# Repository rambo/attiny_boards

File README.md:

View this project on [CADLAB.io](https://cadlab.io/node/904). 

# ATTiny breakout boards

Collection of various more or less prototype board designs for breaking
out SMD ATTinys.

The SMD parts are cheaper than DIP and I've grown tired of drilling holes
anyway, besides this way I can add some essential supporting hardware like
bypass caps and the ISP header on the same board (optionally also xtal)

Arduino support for these chips is available from the [arduino-tiny](https://github.com/rambo/arduino-tiny) project, 
see also [this tutorial](http://hlt.media.mit.edu/?p=1695) by High-Low Tech.

I personally have found using the ArduinoISP a bit hit-and-miss, so I suggest investing on a proper ISP (some of the clones work better
than others but I decided to get a genuine AVRISPmkII after spending an evening battling with ArduinoISP)

## The designs

  - attiny85_bo_1l.brd: this is a very quick design for ATTiny25/45/85 chips meant to be etched at home, thus in one layer. [Picture](https://picasaweb.google.com/lh/photo/0eMphjL9Uqn8iMIKu49FZNMTjNZETYmyPJy0liipFm0?feat=directlink).
  - attiny85_bo.brd: A two-layer design for ATTiny25/45/85 chips that should be generally quite usable. [Picture](https://picasaweb.google.com/lh/photo/wWMrBrGMo7IKX4xKiI6fBtMTjNZETYmyPJy0liipFm0?feat=directlink).
    - First revisions of the board had a silkscreen error, PB1 and PB2 were reversed (my bad).
    - For some reason the very first revision has much nicer silkscreen than the next, they were (likely) manufactured in different batches but I should doublecheck line widths etc.
  - attiny4313_bo.brd: A two-layer design (with a lot of vias so not really doable at home).
    - Got the boards, silkscreen is fine on these, [picture](https://picasaweb.google.com/lh/photo/29UdsFFLtWyybYlaUJ8i69MTjNZETYmyPJy0liipFm0?feat=directlink).
  - attiny84_bo.brd: A two-layer design that should be generally quite usable.
    - Got the boards, silkscreen is fine on these, [picture](https://picasaweb.google.com/lh/photo/29UdsFFLtWyybYlaUJ8i69MTjNZETYmyPJy0liipFm0?feat=directlink).
  - attiny1634_bo.brd: First revision of this board/schematic had a bug in the part definition. Thus a [trace must be cut](https://picasaweb.google.com/lh/photo/p4AA6TQTbEzGxg4LxbUNLtMTjNZETYmyPJy0liipFm0?feat=directlink) and a jumper wire added.
    - arduino-tiny support for this chip is still [experimental](https://github.com/rambo/arduino-tiny/tree/attiny1634)
  - attiny85_pogo_pgm.brd: an attempt to make a pogo-pin programming header that connects directly to ATTiny85 (SOIC) feet.
    - This proved to be rather misguided, it will require very carefull alignment rig but if I get the need of mass programming unsoldered chips I might still do it.

## TODO

  - Add diodes to protect against reverse and over -voltage (with indicator led ?)
  - simple board to break the ISP header into normal 2.54mm pitch pogo-pins in the same order (those pins unfortunately do not fit)
    into the cable connector directly), did this on stripboard and then realized dotboard would have been much better.

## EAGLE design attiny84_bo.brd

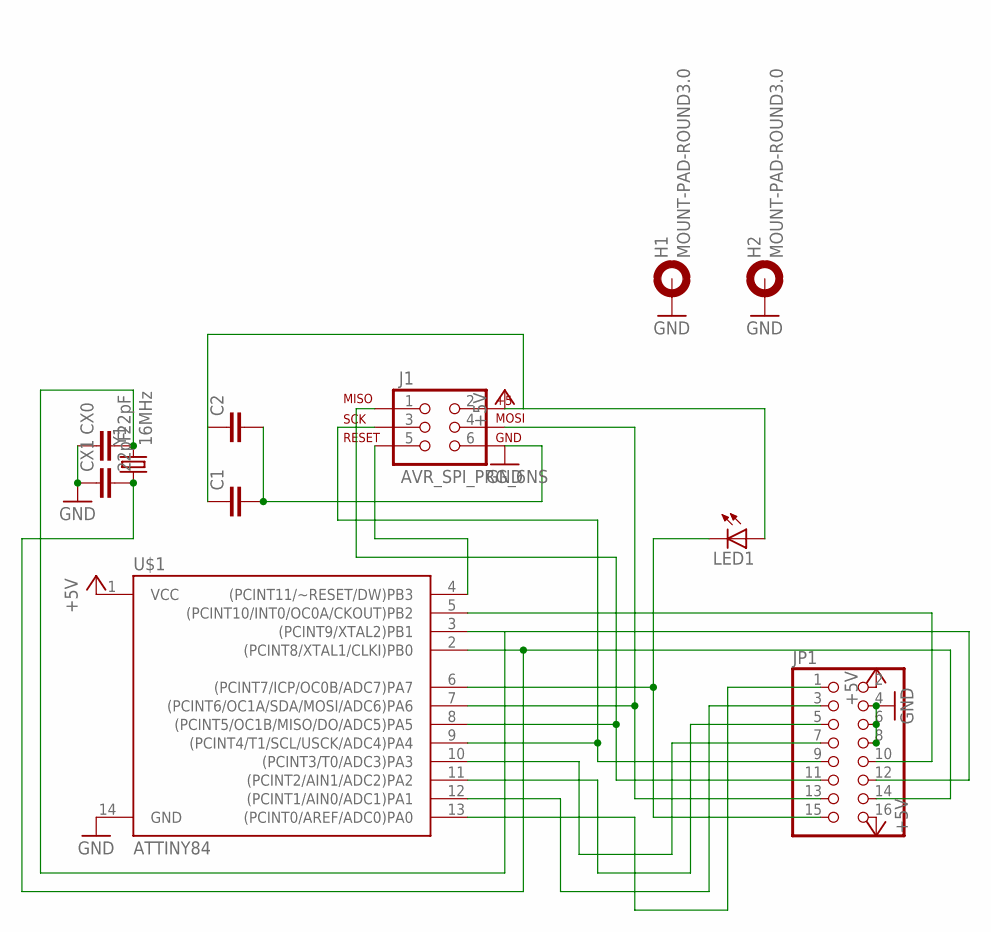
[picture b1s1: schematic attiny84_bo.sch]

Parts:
C1, C2: C-EUC0805; C0805
CX0, CX1: 22pF; C0603
H1, H2: MOUNT-PAD-ROUND3.0; 3,0-PAD
J1: AVR_SPI_PRG_6NS; 2X3-NS
JP1: PINHD-2X8; 2X08
LED1: LED0603; LED-0603
U$1: ATTINY84; SO14
Y1: 16MHz; CRYSTAL-SMD-5X3

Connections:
+5V: C1.1, C2.1, J1.2, JP1.2, JP1.16, LED1.A, U$1.1 (VCC)
GND: C1.2, C2.2, CX0.1, CX1.1, H1.B3,0, H2.B3,0, J1.6, JP1.4, JP1.6, JP1.8, U$1.14 (GND)
PA0: JP1.1, U$1.13 ((PCINT0/AREF/ADC0)PA0)
PA1: JP1.3, U$1.12 ((PCINT1/AIN0/ADC1)PA1)
PA2: JP1.5, U$1.11 ((PCINT2/AIN1/ADC2)PA2)
PA3: JP1.7, U$1.10 ((PCINT3/T0/ADC3)PA3)
PA4/SCL: J1.3, JP1.9, U$1.9 ((PCINT4/T1/SCL/USCK/ADC4)PA4)
PA5/MISO: J1.1, JP1.11, U$1.8 ((PCINT5/OC1B/MISO/DO/ADC5)PA5)
PA6/MOSI: J1.4, JP1.13, U$1.7 ((PCINT6/OC1A/SDA/MOSI/ADC6)PA6)
PA7: JP1.15, LED1.C, U$1.6 ((PCINT7/ICP/OC0B/ADC7)PA7)
PB0/XTAL1: CX1.2, JP1.14, U$1.2 ((PCINT8/XTAL1/CLKI)PB0), Y1.1
PB1/XTAL2: CX0.2, JP1.12, U$1.3 ((PCINT9/XTAL2)PB1), Y1.3 (2)
PB2: JP1.10, U$1.5 ((PCINT10/INT0/OC0A/CKOUT)PB2)
PB3/RESET-: J1.5, U$1.4 ((PCINT11/~RESET/DW)PB3)

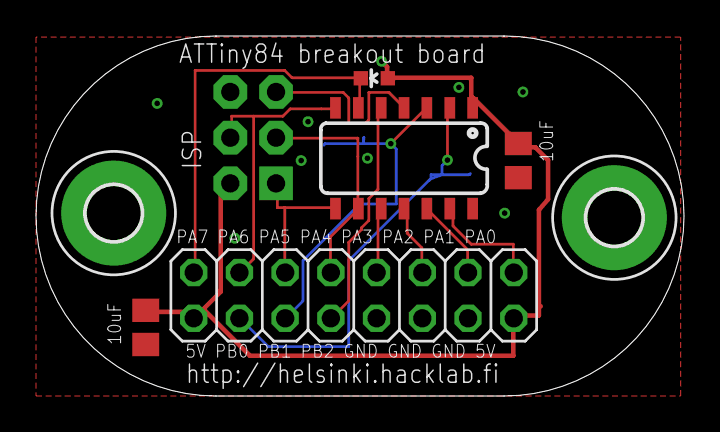
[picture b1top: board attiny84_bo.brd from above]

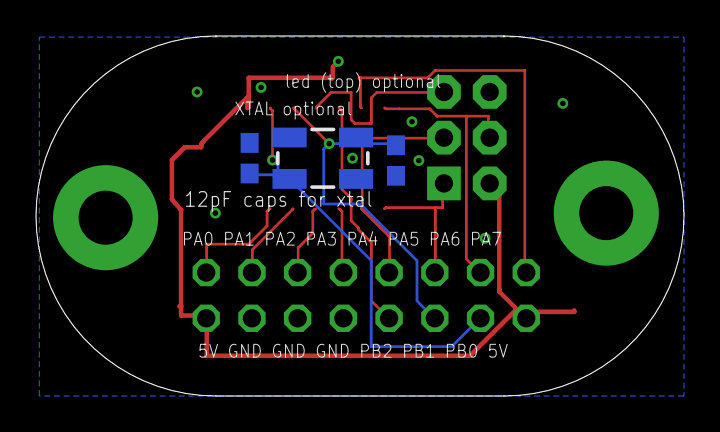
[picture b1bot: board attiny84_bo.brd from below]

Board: 2 copper layers, 36.0 x 20.0 mm, 11 parts (3 on the bottom side), 14 nets.

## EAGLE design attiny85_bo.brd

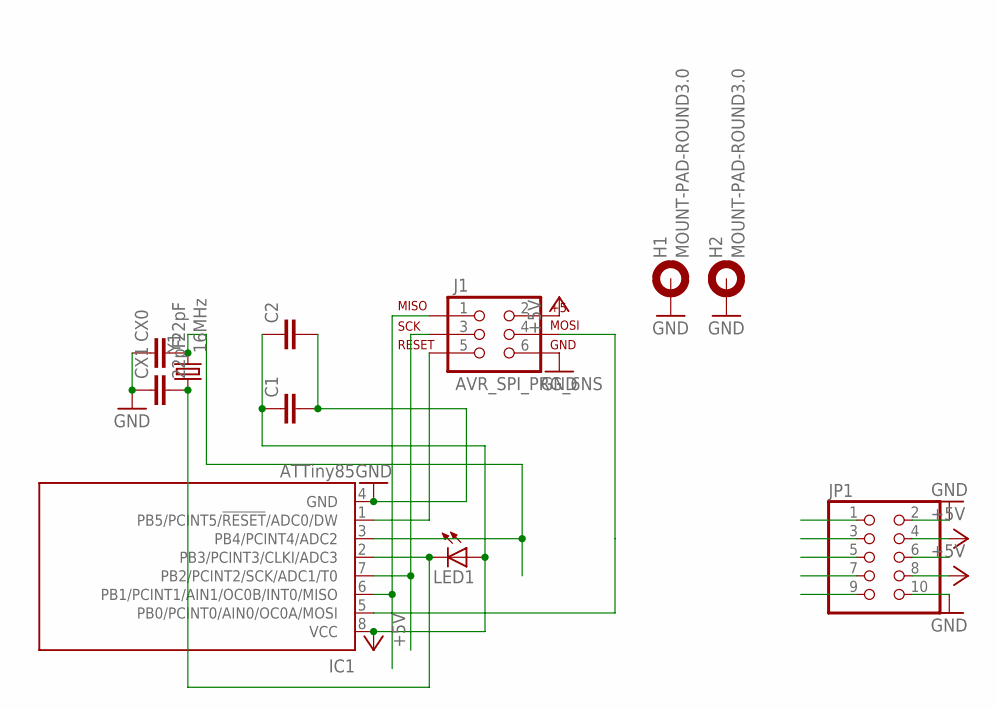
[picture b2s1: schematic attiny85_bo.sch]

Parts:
C1, C2: C-EUC0805; C0805
CX0, CX1: 22pF; C0603
H1, H2: MOUNT-PAD-ROUND3.0; 3,0-PAD
IC1: ATTiny85; 8S2
J1: AVR_SPI_PRG_6NS; 2X3-NS
JP1: PINHD-2X5; 2X05
LED1: LED0603; LED-0603
Y1: 16MHz; CRYSTAL-SMD-5X3

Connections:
+5V: C1.1, C2.1, IC1.8 (VCC), J1.2, JP1.4, JP1.8, LED1.A
GND: C1.2, C2.2, CX0.1, CX1.1, H1.B3,0, H2.B3,0, IC1.4 (GND), J1.6, JP1.2, JP1.10
PB0: IC1.5 (PB0/PCINT0/AIN0/OC0A/MOSI), J1.4, JP1.1
PB1: IC1.6 (PB1/PCINT1/AIN1/OC0B/INT0/MISO), J1.1, JP1.3
PB2: IC1.7 (PB2/PCINT2/SCK/ADC1/T0), J1.3, JP1.5
PB3: CX1.2, IC1.2 (PB3/PCINT3/CLKI/ADC3), JP1.7, LED1.C, Y1.1
PB4: CX0.2, IC1.3 (PB4/PCINT4/ADC2), JP1.9, Y1.3 (2)
PB5: IC1.1 (PB5/PCINT5/!RESET!/ADC0/DW), J1.5, JP1.6

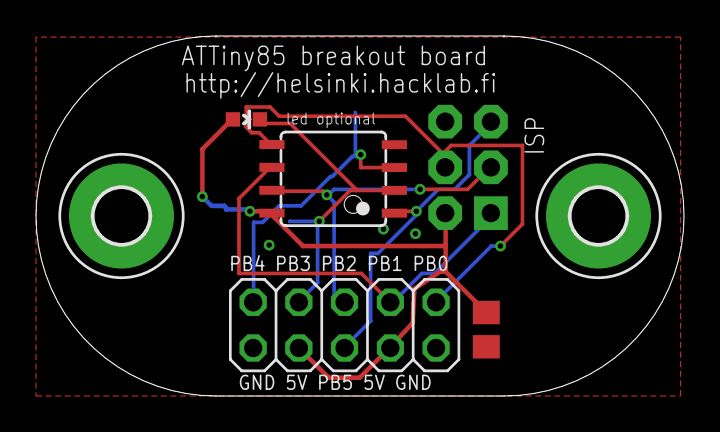
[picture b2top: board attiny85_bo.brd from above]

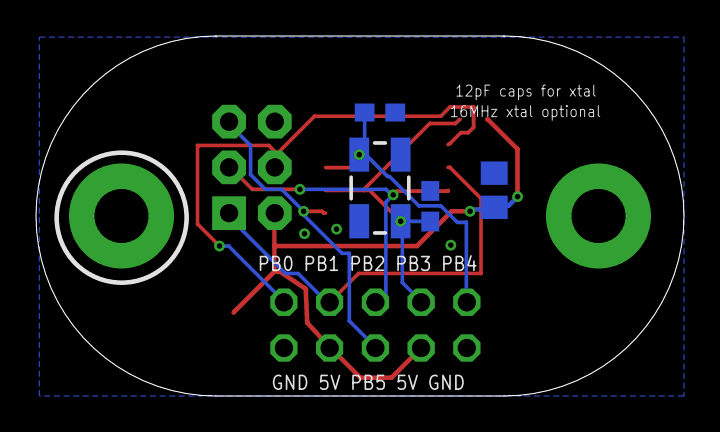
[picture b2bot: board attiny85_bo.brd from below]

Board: 2 copper layers, 36.0 x 20.0 mm, 11 parts (4 on the bottom side), 8 nets.

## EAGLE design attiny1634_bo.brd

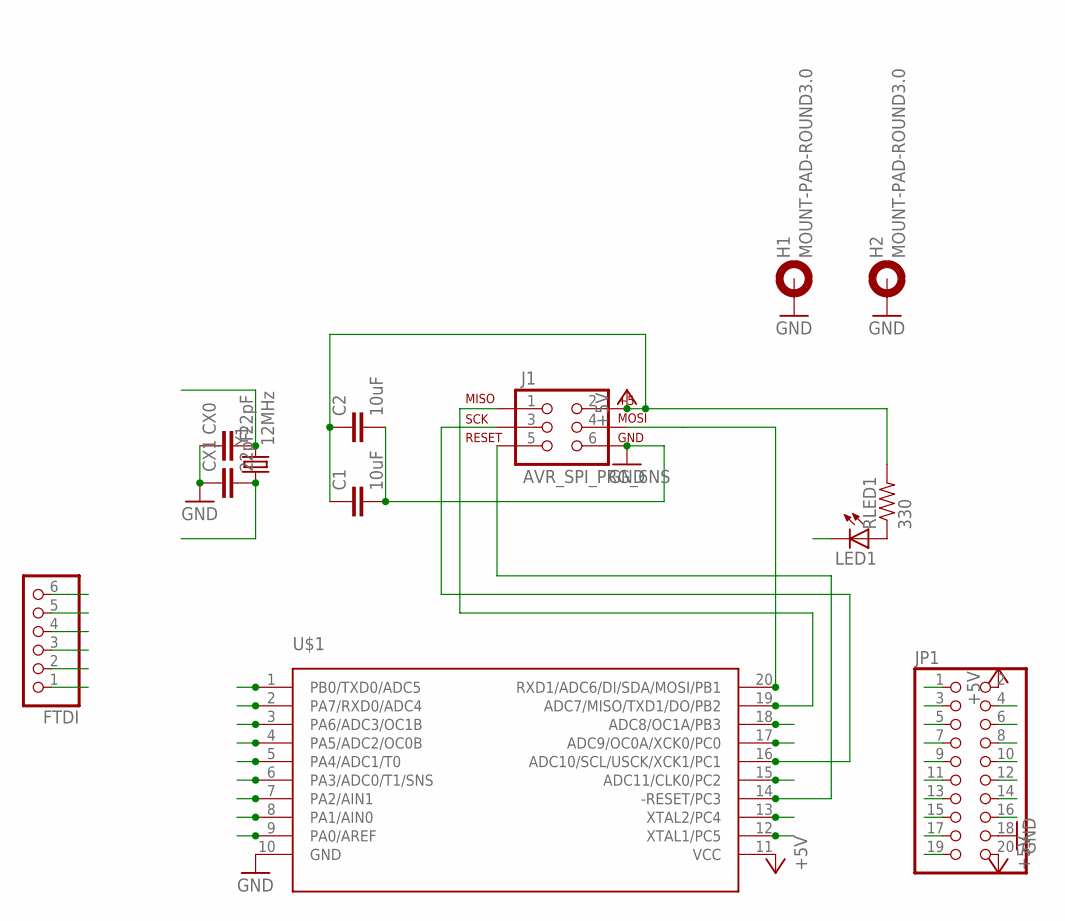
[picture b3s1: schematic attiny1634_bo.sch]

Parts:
C1, C2: 10uF; C0805
CX0, CX1: 22pF; C0603
FTDI: PINHD-1X6; 1X06
H1, H2: MOUNT-PAD-ROUND3.0; 3,0-PAD
J1: AVR_SPI_PRG_6NS; 2X3-NS
JP1: PINHD-2X10; 2X10
LED1: LED0603; LED-0603
RLED1: 330; 0603-RES
U$1: ATTINY1634; SOIC20
Y1: 12MHz; CRYSTAL-SMD-5X3

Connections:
+5V: C1.1, C2.1, FTDI.3, J1.2, JP1.2, JP1.20, RLED1.2, U$1.11 (VCC)
CTS: FTDI.2
GND: C1.2, C2.2, CX0.1, CX1.1, FTDI.1, H1.B3,0, H2.B3,0, J1.6, JP1.18, U$1.10 (GND)
unnamed: LED1.A, RLED1.1
PA0: JP1.5, U$1.9 (PA0/AREF)
PA1: JP1.7, U$1.8 (PA1/AIN0)
PA2: JP1.9, U$1.7 (PA2/AIN1)
PA3: JP1.11, U$1.6 (PA3/ADC0/T1/SNS)
PA4: JP1.13, U$1.5 (PA4/ADC1/T0)
PA5: JP1.15, U$1.4 (PA5/ADC2/OC0B)
PA6: JP1.17, U$1.3 (PA6/ADC3/OC1B)
PA7/RX0: FTDI.4, JP1.19, U$1.2 (PA7/RXD0/ADC4)
PB0/TXD0: FTDI.5, JP1.16, U$1.1 (PB0/TXD0/ADC5)
PB1/MOSI/ADC6: J1.4, JP1.14, U$1.20 (RXD1/ADC6/DI/SDA/MOSI/PB1)
PB2/ADC7/TX1: J1.1, JP1.12, U$1.19 (ADC7/MISO/TXD1/DO/PB2)
PB3/ADC8/OC1A: JP1.10, U$1.18 (ADC8/OC1A/PB3)
PC0/ADC9/OC0A: JP1.8, LED1.C, U$1.17 (ADC9/OC0A/XCK0/PC0)
PC1/SCL/ADC10: J1.3, JP1.1, U$1.16 (ADC10/SCL/USCK/XCK1/PC1)
PC2/ADC11: JP1.3, U$1.15 (ADC11/CLK0/PC2)
PC3/-RESET: FTDI.6, J1.5, U$1.14 (-RESET/PC3)
PC4/XTAL2: CX0.2, JP1.6, U$1.13 (XTAL2/PC4), Y1.3 (2)
PC5/XTAL1: CX1.2, JP1.4, U$1.12 (XTAL1/PC5), Y1.1

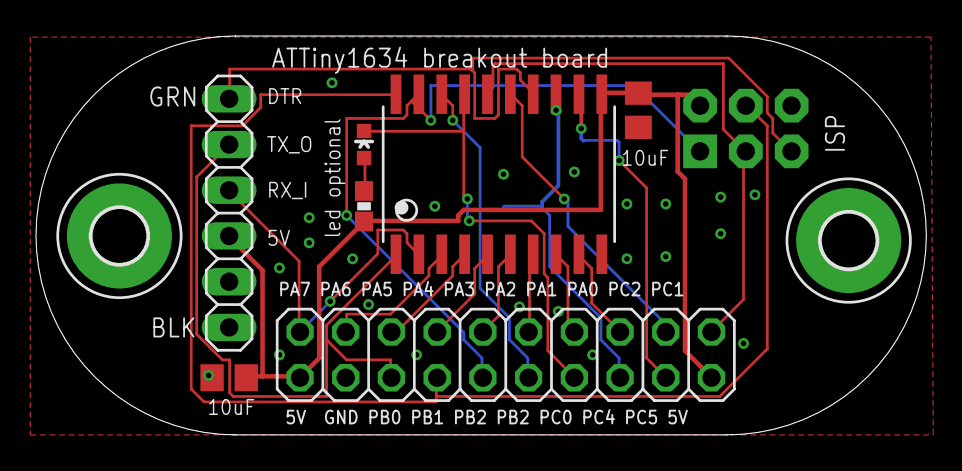
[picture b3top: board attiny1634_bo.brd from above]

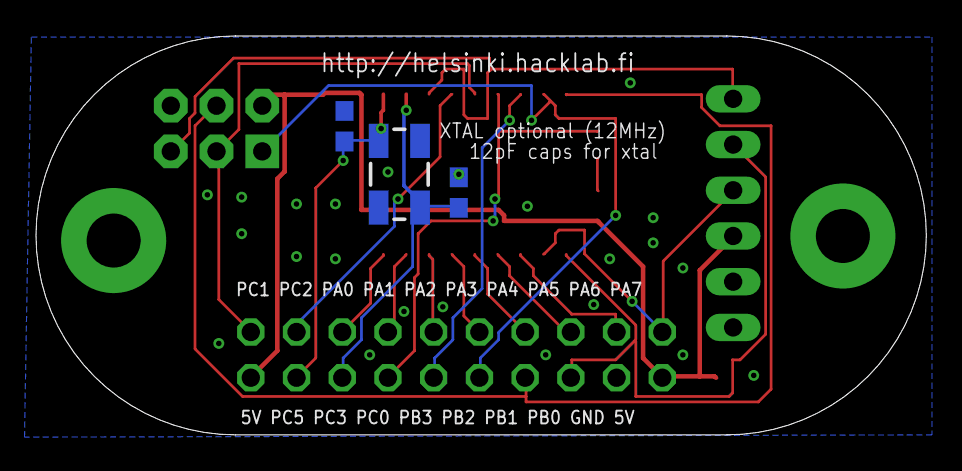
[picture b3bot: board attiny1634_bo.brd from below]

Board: 2 copper layers, 49.5 x 22.2 mm, 13 parts (3 on the bottom side), 21 nets.

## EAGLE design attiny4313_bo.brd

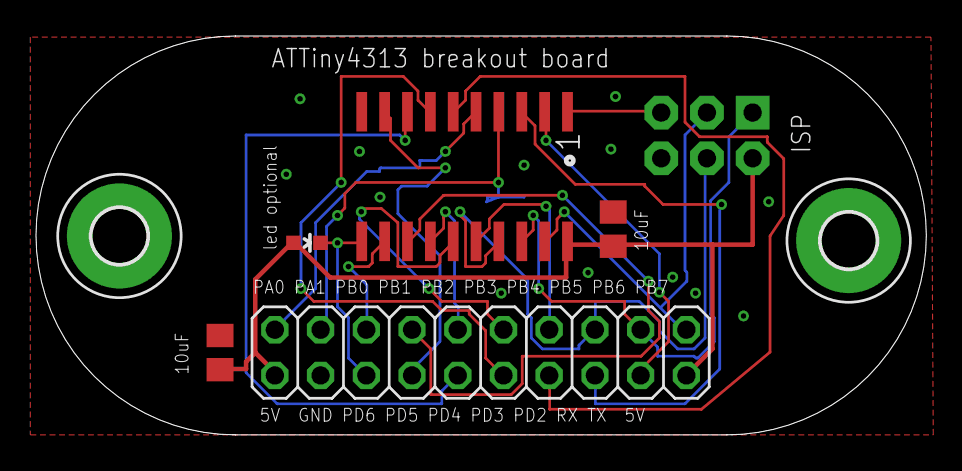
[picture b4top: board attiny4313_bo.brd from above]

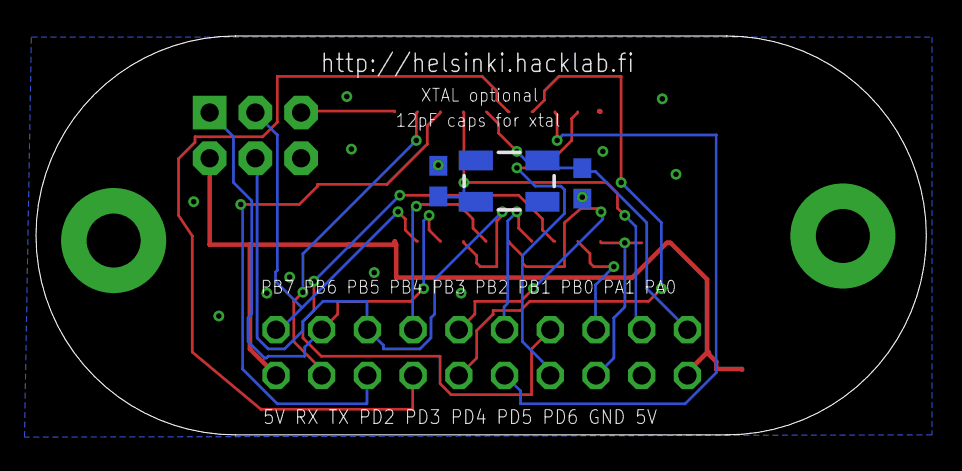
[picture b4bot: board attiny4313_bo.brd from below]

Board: 2 copper layers, 49.5 x 22.2 mm, 11 parts (3 on the bottom side), 20 nets.

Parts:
C1, C2: C0805
CX0, CX1: 22pF; C0603
H1, H2: MOUNT-PAD-ROUND3.0; 3,0-PAD
J1: AVR_SPI_PRG_6NS; 2X3-NS
JP1: 2X10
LED1: LED-0603
U$1: ATTINY2313A; SOP20
Y1: 16MHz; CRYSTAL-SMD-5X3

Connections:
+5V: C1.1, C2.1, J1.2, JP1.2, JP1.20, LED1.A, U$1.20
GND: C1.2, C2.2, CX0.1, CX1.1, H1.B3,0, H2.B3,0, J1.6, JP1.18, U$1.10
PA0/XTAL1: CX0.2, JP1.19, U$1.5, Y1.3
PA1/XTAL2: CX1.2, JP1.17, U$1.4, Y1.1
PA2/RESET-: J1.5, U$1.1
PB0: JP1.15, U$1.12
PB1: JP1.13, U$1.13
PB2: JP1.11, U$1.14
PB3: JP1.9, U$1.15
PB4: JP1.7, U$1.16
PB5/MOSI: J1.4, JP1.5, U$1.17
PB6/MISO: J1.1, JP1.3, U$1.18
PB7/SCL: J1.3, JP1.1, U$1.19
PD0/RDX: JP1.4, U$1.2
PD1/TXD: JP1.6, U$1.3
PD2: JP1.8, U$1.6
PD3: JP1.10, U$1.7
PD4: JP1.12, U$1.8
PD5: JP1.14, U$1.9
PD6: JP1.16, LED1.C, U$1.11

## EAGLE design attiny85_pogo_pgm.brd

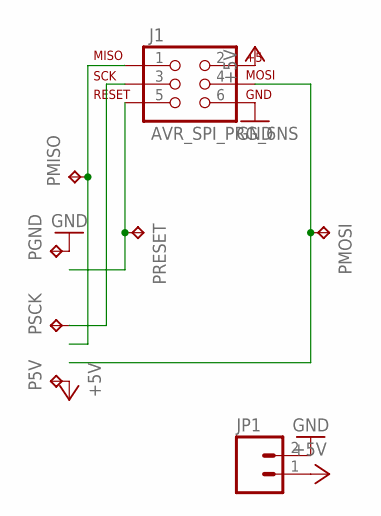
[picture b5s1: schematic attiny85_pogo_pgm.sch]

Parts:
J1: AVR_SPI_PRG_6NS; 2X3-NS
JP1: M02PTH; 1X02
P5V: TPTP12R; TP12R
PGND: TPTP12R; TP12R
PMISO: TPTP12R; TP12R
PMOSI: TPTP12R; TP12R
PRESET: TPTP12R; TP12R
PSCK: TPTP12R; TP12R

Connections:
+5V: J1.2, JP1.1, P5V.TP
GND: J1.6, JP1.2, PGND.TP
IN1/MISO: J1.1, PMISO.TP
RESET-: J1.5, PRESET.TP
SCL/SCK: J1.3, PSCK.TP
SDA/MOSI: J1.4, PMOSI.TP

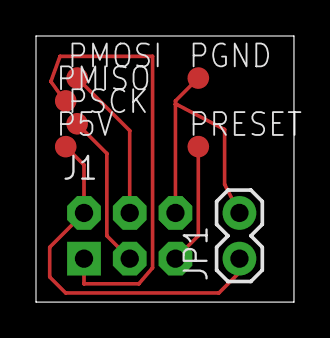
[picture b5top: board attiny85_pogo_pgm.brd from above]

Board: 1 copper layer, 14.3 x 14.8 mm, 8 parts (0 on the bottom side), 6 nets.

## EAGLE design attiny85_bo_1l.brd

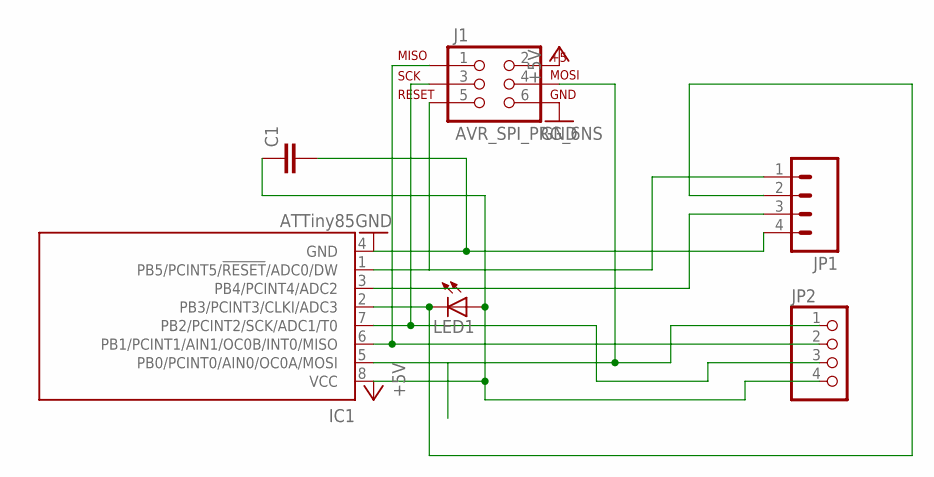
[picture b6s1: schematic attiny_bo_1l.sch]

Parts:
C1: C-EUC0805; C0805
IC1: ATTiny85; 8S2
J1: AVR_SPI_PRG_6NS; 2X3-NS
JP1: M041X04_NO_SILK; 1X04_NO_SILK
JP2: PINHD-1X4; 1X04
LED1: LED0603; LED-0603

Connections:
+5V: C1.1, IC1.8 (VCC), J1.2, JP2.4, LED1.A
GND: C1.2, IC1.4 (GND), J1.6, JP1.4
IN1/MISO: IC1.6 (PB1/PCINT1/AIN1/OC0B/INT0/MISO), J1.1, JP2.2
unnamed: IC1.3 (PB4/PCINT4/ADC2), JP1.3
unnamed: IC1.2 (PB3/PCINT3/CLKI/ADC3), JP1.2, LED1.C
unnamed: IC1.1 (PB5/PCINT5/!RESET!/ADC0/DW), J1.5, JP1.1
SCL/SCK: IC1.7 (PB2/PCINT2/SCK/ADC1/T0), J1.3, JP2.3
SDA/MOSI: IC1.5 (PB0/PCINT0/AIN0/OC0A/MOSI), J1.4, JP2.1

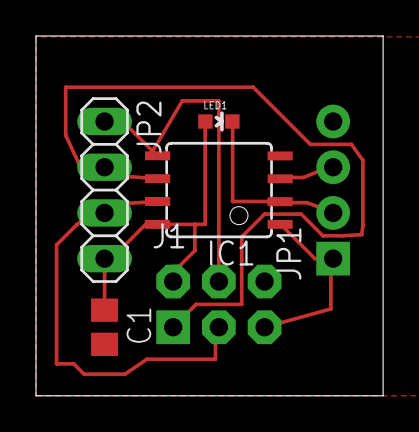
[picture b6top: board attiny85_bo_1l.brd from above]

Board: 1 copper layer, 19.3 x 20.0 mm, 6 parts (0 on the bottom side), 8 nets.

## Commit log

2012-08-14 simple breakout board for attiny25/45/85
2012-08-14 name to reflect correct chip
2012-08-14 attempt to make a programming header that connects to soic attiny85 pins with pogo-pins (in retrospect a clip would probably work better...)
2012-08-14 a much nicer design, I have a set of these on their way from Seeed
2012-08-14 descriptions of the boards to the README
2012-08-14 mark the chip type to the text
2012-08-14 started working on attiny84 breakout board
2012-08-14 initial placement
2012-08-14 routing settings
2012-08-14 routed
2012-08-14 signal names
2012-08-14 second 5v input
2012-08-14 pin legend
2012-08-14 some labels
2012-08-14 typo fix
2012-08-14 xtal xap size
2012-08-14 move the other cap near the other 5v input
2012-08-14 started working on attiny4313 version
2012-08-14 signals v1, probably bad
2012-08-14 pin identifiers
2012-08-14 minor adjustments
2012-08-14 two new designs
2012-08-18 protection diodes might be a good idea...
2012-08-18 pb1/2 were reversed on silkscreen
2012-08-18 trivial sketch to blink the led on the attiny85 boards
2012-08-18 clarify that this is for the 85/45/25 chips
2012-08-18 silkscreen fix and adjusted readme
2012-08-18 clearer markings for the first pins
2012-08-20 added reminder of the xtal pins
2012-09-01 photos of the new boards
2012-09-01 notes on arduino support
2012-09-01 minor fixes
2012-10-08 pin mappings
2012-11-12 copy the 4313 as base for this breakout
2012-11-12 QnD library for this IC
2012-11-12 use the new part and remove old wires from schematic
2012-11-12 12MHz max speed for this part
2012-11-12 ripup the traces, needs to be rerouted anyway
2012-11-12 minor fixes to the lib, connected programming signals and xtal
2012-11-12 connected portA
2012-11-12 typo fixes, connected portB
2012-11-12 more signals
2012-11-12 adjusted texts and positions
2012-11-12 changed the board title
2012-11-12 autorouted
2012-11-12 minor manual routing adjustment, I am not 100% happy with this though
2012-11-12 adjusted xtal position
2012-11-12 pre-routed the clock
2012-11-12 freeroute.net autorouted (and some vias added)
2012-11-12 moar GND
2012-11-12 small adjustment for better isolation
2012-11-12 I think it is now good enough
2012-12-15 shite, the MOSI is was marked to wrong pin...
2012-12-15 add a resistor for the led and move the mcu group right, in preparation for adding a uart header
2012-12-15 space for cable
2012-12-15 added Arduino style FTDI UART header
2012-12-15 manually routed the xtal
2012-12-15 Eagle autorouted
2012-12-15 ignore stopmask warnigns
2012-12-15 args, the PORTA pins did not get reconnected when I fixed the mcu part
2012-12-15 re-routed the xtal
2013-01-01 Fixed some links added ATTiny1634 description
2013-01-13 pin numers from core source comments
2013-01-13 use same naming scheme
2013-03-10 remaking the attiny85 baord so it is more easily connected to stripboard via 90deg pin header
2013-03-10 route the crystals manually
2013-03-10 let autorouter take care of the rest
2013-03-10 minor adjustment
2013-03-10 very quick and dirty prog header adjustment to attiny84 board
2013-04-13 QnD test sketch for digitalwrite
2013-06-08 how to connect bus pirate as ISP
2014-12-11 Update pad spacing for attiny1634 MLF20 to better match data sheet
2018-04-20 Backlink to CADLAB.io has been added.

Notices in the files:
parts and their libraries:
SparkFun-Connectors: Licensing: CC v3.0 Share-Alike You are welcome to use this library for commercial purposes.
